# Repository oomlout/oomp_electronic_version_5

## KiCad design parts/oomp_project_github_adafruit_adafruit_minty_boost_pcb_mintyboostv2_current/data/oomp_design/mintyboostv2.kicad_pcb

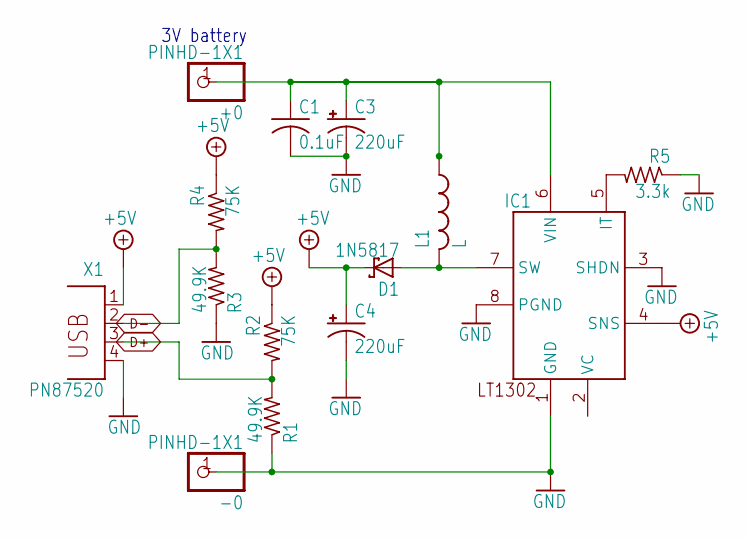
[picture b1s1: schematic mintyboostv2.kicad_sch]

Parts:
+0: PINHD-1X1; 1X01
-0: PINHD-1X1; 1X01
C1: 0.1uF; C025-025X050
C3, C4: 220uF; E2,5-5
D1: 1N5817; DO41-7
IC1: LT1302; DIL08
L1: L; 6000
R1, R3: 49.9K; 0204_5
R2, R4: 75K; 0204_5
R5: 3.3k; 0204_5
X1: PN87520

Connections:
+5V: C4.+, D1.C, IC1.4 (SNS), R2.1, R4.1, X1.1
BATT+: +0.1, C1.1, C3.+, IC1.6 (VIN), L1.1
D+: R1.2, R2.2, X1.3
D-: R3.2, R4.2, X1.2
GND: -0.1, C1.2, C3.-, C4.-, IC1.1 (GND), IC1.3 (SHDN), IC1.8 (PGND), R1.1, R3.1, R5.1, X1.4
unnamed: IC1.5 (IT), R5.2
unnamed: D1.A, IC1.7 (SW), L1.2

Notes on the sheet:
3V battery

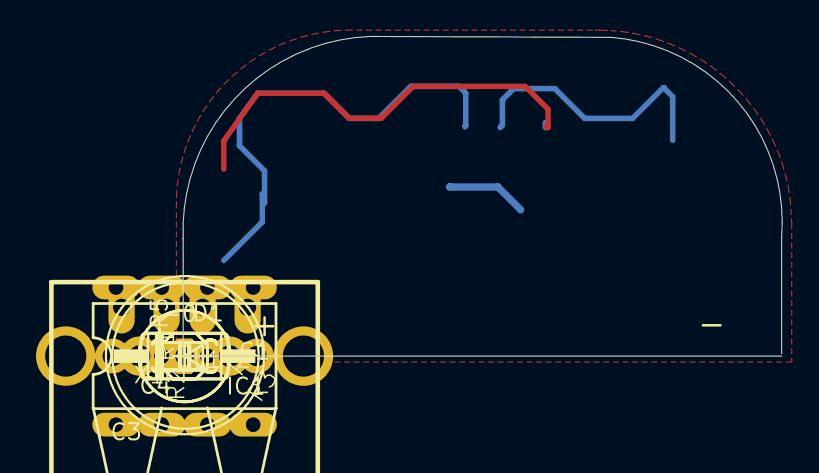
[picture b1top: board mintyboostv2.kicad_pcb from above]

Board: 16 copper layers, 33.3 x 17.8 mm, 14 parts (0 on the bottom side), 7 nets.

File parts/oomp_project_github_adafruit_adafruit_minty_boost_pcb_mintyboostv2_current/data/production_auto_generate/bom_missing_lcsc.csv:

Designator,Comment,Footprint,OOMP ID,Reason
C1,0.1uF,mintyboostv2-import-fps:C025-025X050,,No verified LCSC part number
C3,220uF,"mintyboostv2-import-fps:E2,5-5",,No verified LCSC part number
C4,220uF,"mintyboostv2-import-fps:E2,5-5",,No verified LCSC part number
D1,1N5817,mintyboostv2-import-fps:DO41-7,,No verified LCSC part number
IC1,LT1302,mintyboostv2-import-fps:DIL08,,No verified LCSC part number
L1,L,mintyboostv2-import-fps:6000,,No verified LCSC part number
R1,49.9K,mintyboostv2-import-fps:0204_5,,No verified LCSC part number
R2,75K,mintyboostv2-import-fps:0204_5,,No verified LCSC part number
R3,49.9K,mintyboostv2-import-fps:0204_5,,No verified LCSC part number
R4,75K,mintyboostv2-import-fps:0204_5,,No verified LCSC part number
R5,3.3k,mintyboostv2-import-fps:0204_5,,No verified LCSC part number
X1,,mintyboostv2-import-fps:PN87520,,No verified LCSC part number

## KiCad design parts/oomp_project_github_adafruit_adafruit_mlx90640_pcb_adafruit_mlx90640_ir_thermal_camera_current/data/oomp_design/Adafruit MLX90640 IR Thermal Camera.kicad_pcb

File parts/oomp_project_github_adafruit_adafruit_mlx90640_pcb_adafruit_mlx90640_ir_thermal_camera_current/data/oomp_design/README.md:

# OOMP KiCad design copy

Open `Adafruit MLX90640 IR Thermal Camera.kicad_pro` (or the `.kicad_pcb` / `.kicad_sch`) in KiCad. Local OOMP libraries are under `libraries/`. Original inputs are preserved in [../original/](../original/).

Only verified unchanged installed KiCad defaults were renamed. Modified, custom, unmatched and unavailable items remain unchanged. Soldering variants are never swapped during conversion. Existing pad coordinates, nets and UUIDs are preserved.

See [conversion_report.yaml](conversion_report.yaml) for every conversion and skip. Copy this directory before editing; regeneration refuses to overwrite edited design files.

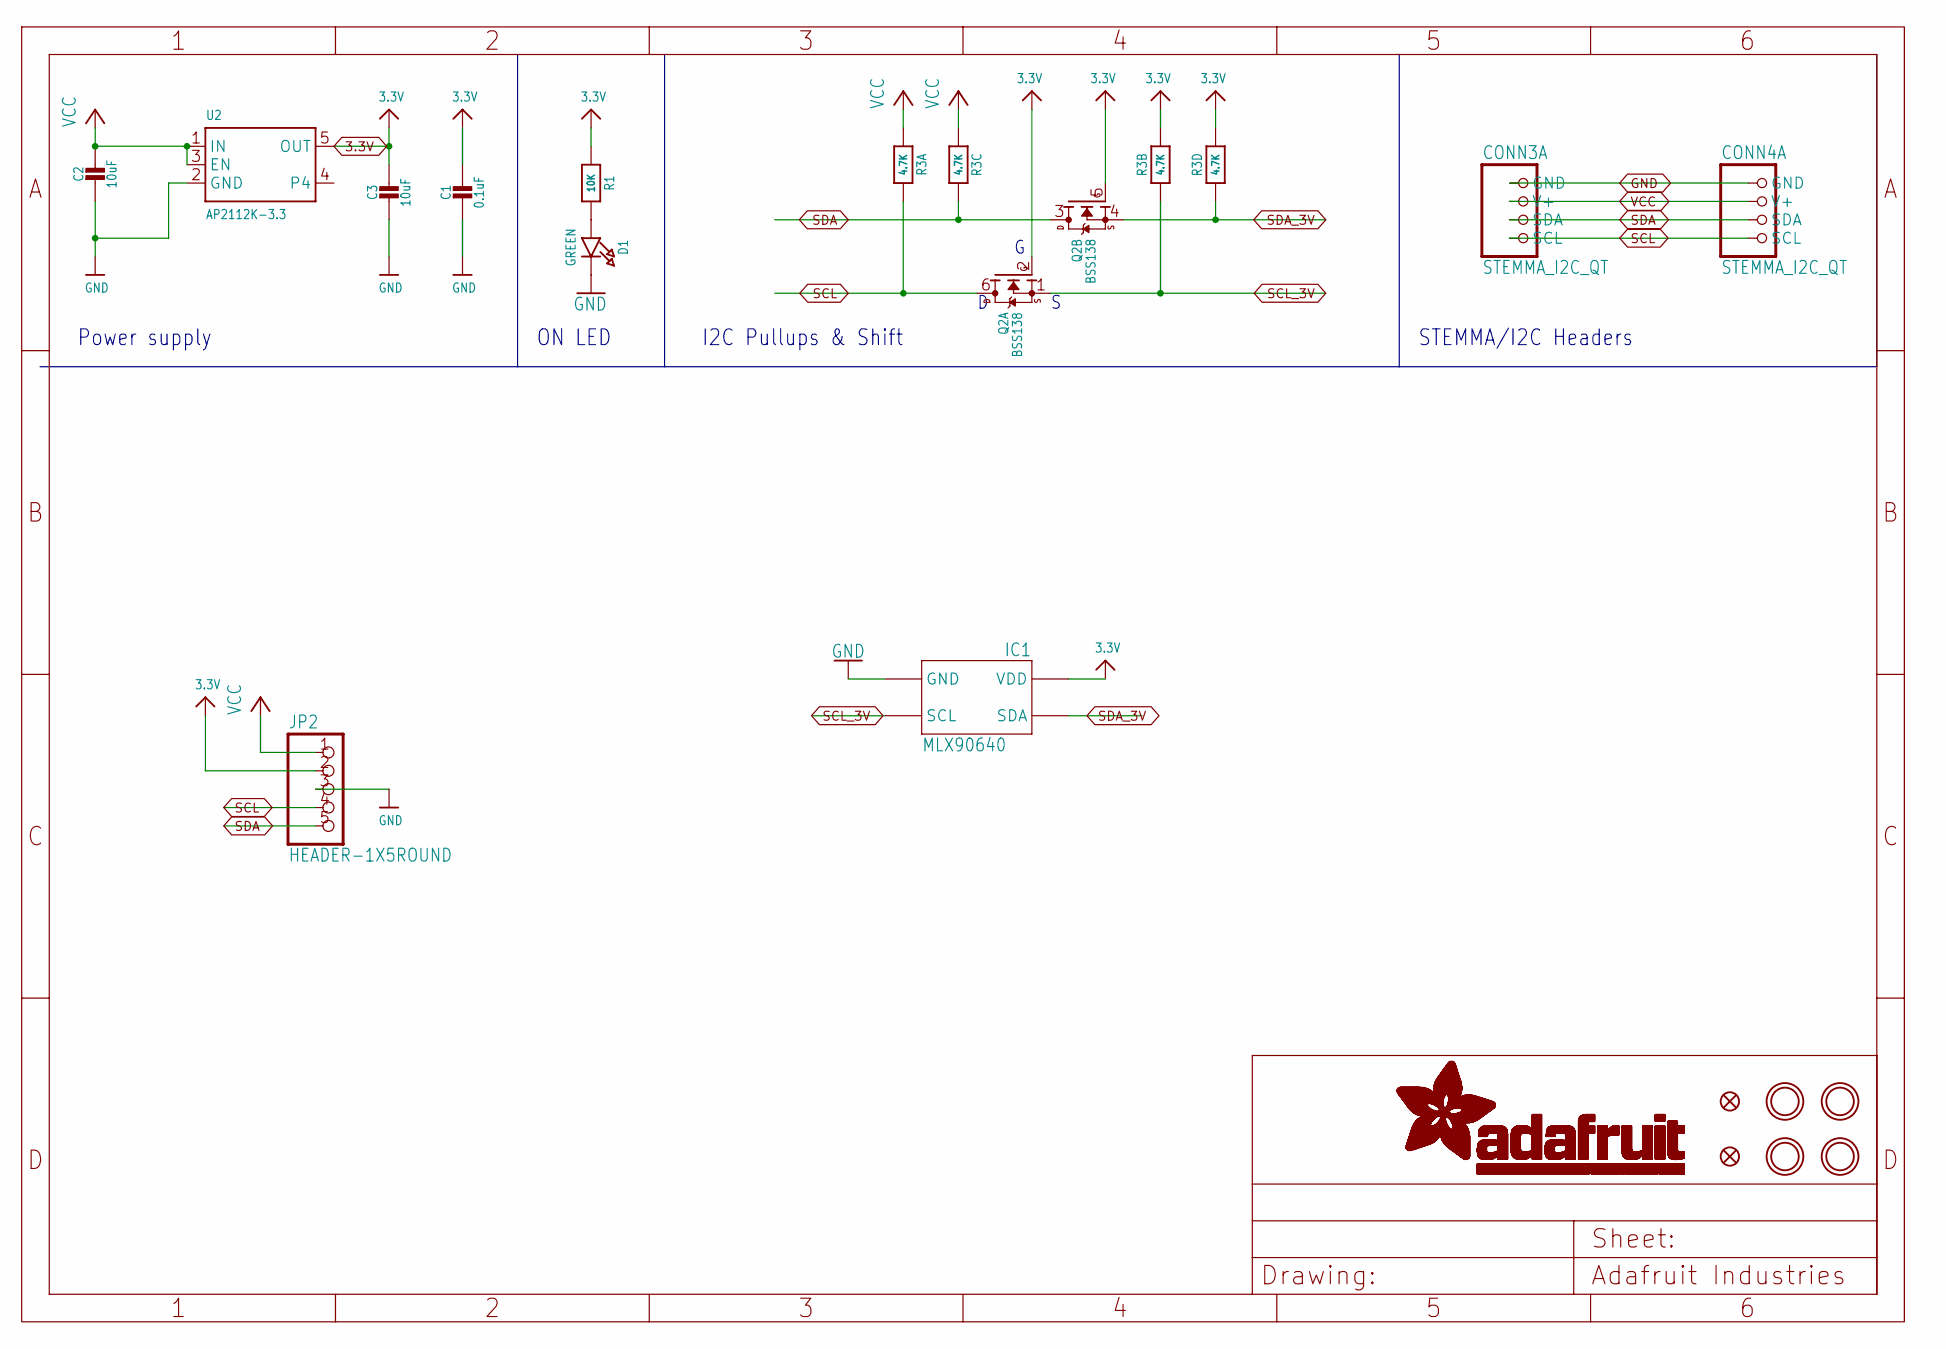
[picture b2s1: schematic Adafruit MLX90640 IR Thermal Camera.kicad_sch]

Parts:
C1: 0.1uF; 0603-NO
C2, C3: 10uF; 0805-NO
CONN3, CONN4: STEMMA_I2C_QT; JST_SH4
D1: GREEN; CHIPLED_0603_NOOUTLINE
FID3, FID4: FIDUCIAL_1MM
IC1: MLX90640
JP2: HEADER-1X5ROUND; 1X05_ROUND
Q2: BSS138; SOT363
R1: 10K; 0603-NO
R3: 4.7K; RESPACK_4X0603
U2: AP2112K-3.3; SOT23-5
U$1, U$17, U$19, U$21: MOUNTINGHOLE2.5; MOUNTINGHOLE_2.5_PLATED

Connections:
3.3V: C1.1, C3.1, IC1.VDD, JP2.2, Q2.2 (G), Q2.5 (G), R1.1, R3.2 (1), R3.4 (1), U2.5 (OUT)
GND: C1.2, C2.2, C3.2, CONN3.1 (GND), CONN4.1 (GND), D1.C, IC1.GND, JP2.3, U2.2 (GND)
unnamed: D1.A, R1.2
SCL: CONN3.4 (SCL), CONN4.4 (SCL), JP2.4, Q2.6 (D), R3.8 (2)
SCL_3V: IC1.SCL, Q2.1 (S), R3.7 (2)
SDA: CONN3.3 (SDA), CONN4.3 (SDA), JP2.5, Q2.3 (D), R3.6 (2)
SDA_3V: IC1.SDA, Q2.4 (S), R3.5 (2)
VCC: C2.1, CONN3.2 (V+), CONN4.2 (V+), JP2.1, R3.1, R3.3 (1), U2.1 (IN), U2.3 (EN)

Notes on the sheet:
I2C Pullups & Shift
STEMMA/I2C Headers
ON LED
Power supply

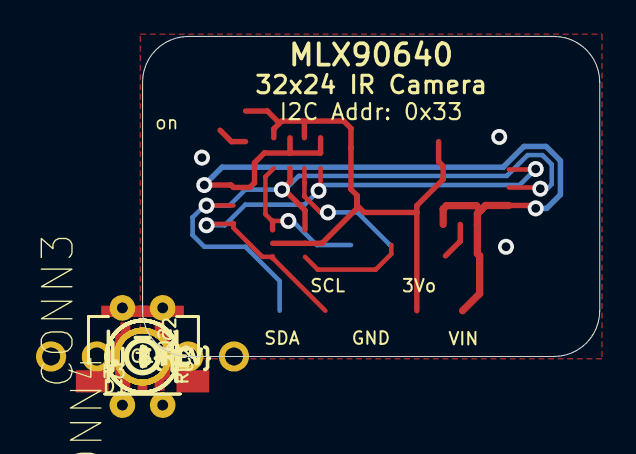
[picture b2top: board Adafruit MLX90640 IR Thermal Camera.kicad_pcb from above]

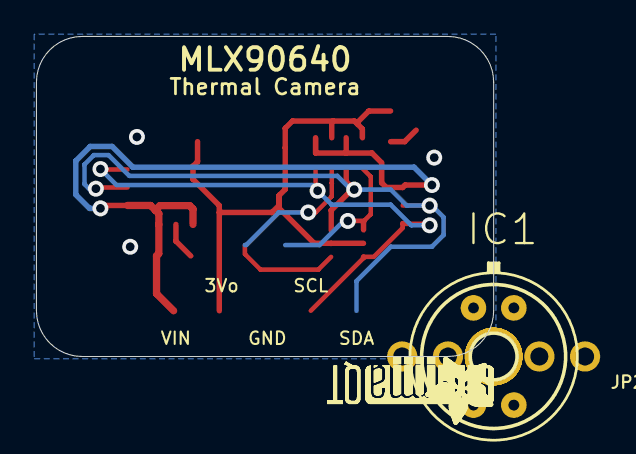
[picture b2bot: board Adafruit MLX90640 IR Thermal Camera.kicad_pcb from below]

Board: 2 copper layers, 25.4 x 17.8 mm, 23 parts (6 on the bottom side), 8 nets.

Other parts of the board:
U$4, U$22: ADAFRUIT_3.5MM
U$25: PCBFEAT-REV-040
U$30, U$31: STEMMAQT

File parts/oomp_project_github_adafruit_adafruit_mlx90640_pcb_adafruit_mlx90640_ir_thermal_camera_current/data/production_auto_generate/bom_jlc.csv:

Comment,Designator,Footprint,LCSC Part #
,JP2,Adafruit MLX90640 IR Thermal Camera-import-fps:1X05_ROUND,C42431835
,"U$4,U$22",Adafruit MLX90640 IR Thermal Camera-import-fps:ADAFRUIT_3.5MM,
,U$25,Adafruit MLX90640 IR Thermal Camera-import-fps:PCBFEAT-REV-040,
,"U$30,U$31",Adafruit MLX90640 IR Thermal Camera-import-fps:STEMMAQT,
0.1uF,C1,Adafruit MLX90640 IR Thermal Camera-import-fps:0603-NO,C14663
10K,R1,Adafruit MLX90640 IR Thermal Camera-import-fps:0603-NO,C98220
10uF,"C2,C3",Adafruit MLX90640 IR Thermal Camera-import-fps:0805-NO,
4.7K,R3,Adafruit MLX90640 IR Thermal Camera-import-fps:RESPACK_4X0603,C23162
AP2112K-3.3,U2,Adafruit MLX90640 IR Thermal Camera-import-fps:SOT23-5,
BSS138,Q2,Adafruit MLX90640 IR Thermal Camera-import-fps:SOT363,
GREEN,D1,Adafruit MLX90640 IR Thermal Camera-import-fps:CHIPLED_0603_NOOUTLINE,
MLX90640,IC1,Adafruit MLX90640 IR Thermal Camera-import-fps:MLX90640,
STEMMA_I2C_QT,"CONN3,CONN4",Adafruit MLX90640 IR Thermal Camera-import-fps:JST_SH4,C160404

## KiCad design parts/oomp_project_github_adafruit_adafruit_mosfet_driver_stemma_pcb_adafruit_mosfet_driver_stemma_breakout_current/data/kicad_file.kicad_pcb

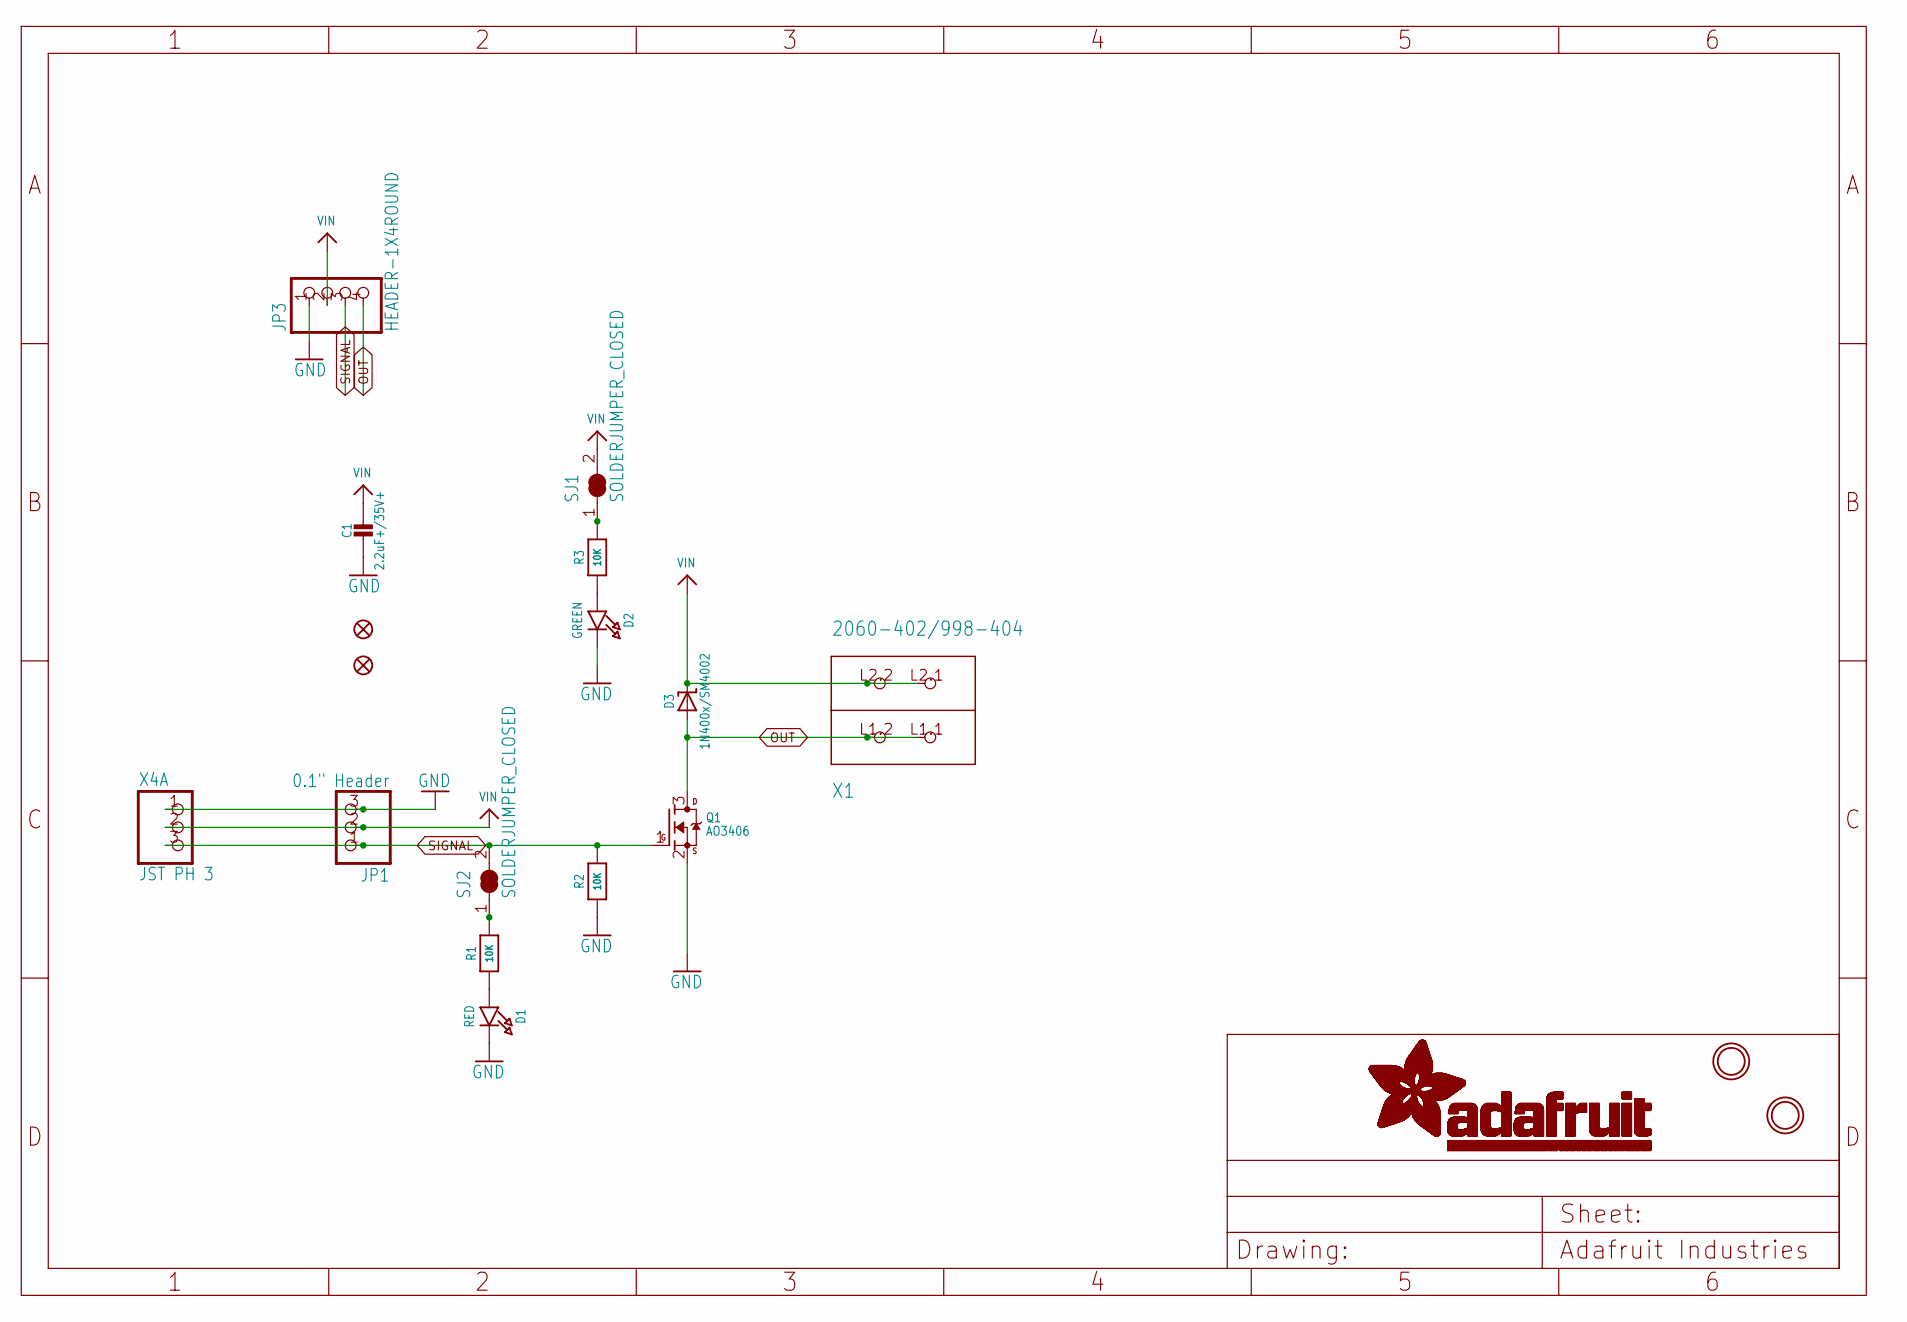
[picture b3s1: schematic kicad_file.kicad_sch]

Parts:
C1: 2.2uF+/35V+; 0805-NO
D1: RED; CHIPLED_0603_NOOUTLINE
D2: GREEN; CHIPLED_0603_NOOUTLINE
D3: 1N400x/SM4002; SOD-123
FID2, FID3: FIDUCIAL_1MM
JP1: 0.1" Header; 1X03_OVAL
JP3: HEADER-1X4ROUND; 1X04_ROUND
Q1: AO3406; SOT23-WIDE
R1, R2, R3: 10K; 0603-NO
SJ1, SJ2: SOLDERJUMPER_CLOSED; SOLDERJUMPER_CLOSEDWIRE
U$1, U$8: MOUNTINGHOLE2.5; MOUNTINGHOLE_2.5_PLATED
X1: 2060-402/998-404; P-2060-402_998-404
X4: JST PH 3; JSTPH3

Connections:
GND: C1.2, D1.C, D2.C, JP1.3, JP3.1, Q1.2 (S), R2.1, X4.1
unnamed: R3.2, SJ1.1
unnamed: D1.A, R1.1
unnamed: R1.2, SJ2.1
unnamed: D2.A, R3.1
OUT: D3.A, JP3.4, Q1.3 (D), X1.L1.1 (P1.1), X1.L1.2 (P1.2)
SIGNAL: JP1.1, JP3.3, Q1.1 (G), R2.2, SJ2.2, X4.3
VIN: C1.1, D3.C, JP1.2, JP3.2, SJ1.2, X1.L2.1 (P2.1), X1.L2.2 (P2.2), X4.2

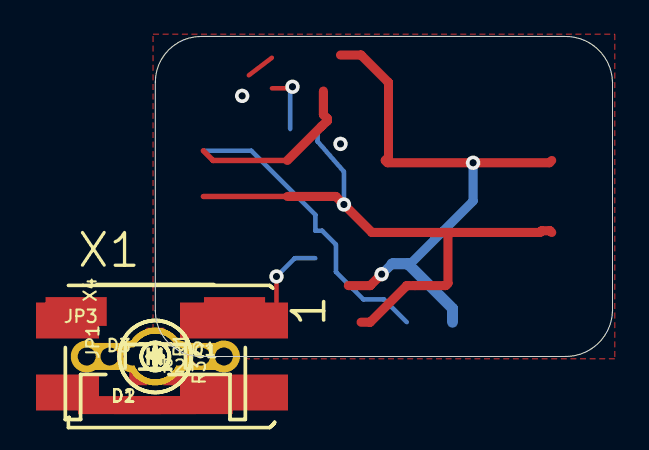
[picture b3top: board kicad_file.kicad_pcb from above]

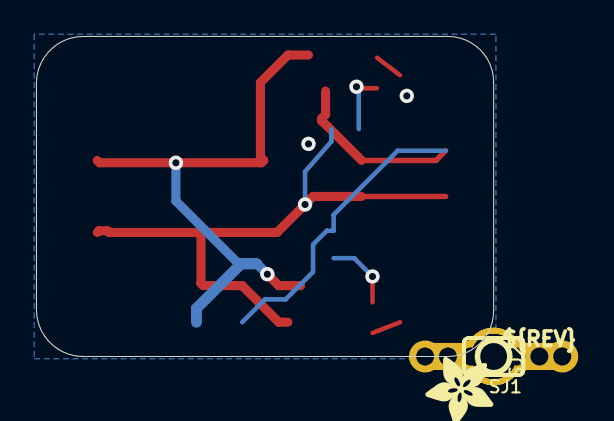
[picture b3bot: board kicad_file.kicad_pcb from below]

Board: 16 copper layers, 25.4 x 17.8 mm, 36 parts (15 on the bottom side), 8 nets.

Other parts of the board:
PLABEL0: PLABEL0
PLABEL1: PLABEL1
PLABEL2: PLABEL2
PLABEL3: PLABEL3
PLABEL4: PLABEL4
PLABEL5: PLABEL5
PLABEL6: PLABEL6
PLABEL7: PLABEL7
PLABEL8: PLABEL8
PLABEL9: PLABEL9
PLABEL10: PLABEL10
PLABEL11: PLABEL11
PLABEL12: PLABEL12
PLABEL13: PLABEL13
U$3: SYMBOL_PLUS
U$5: PCBFEAT-REV-040
U$9: SYMBOL_MINUS
U$12: ADAFRUIT_3.5MM

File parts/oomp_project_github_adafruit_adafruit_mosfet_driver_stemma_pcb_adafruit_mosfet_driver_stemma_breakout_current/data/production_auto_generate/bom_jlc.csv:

Comment,Designator,Footprint,LCSC Part #
,JP3,Adafruit MOSFET Driver STEMMA Breakout-import-fps:1X04_ROUND,C42431795
,U$12,Adafruit MOSFET Driver STEMMA Breakout-import-fps:ADAFRUIT_3.5MM,
,U$5,Adafruit MOSFET Driver STEMMA Breakout-import-fps:PCBFEAT-REV-040,
,PLABEL0,Adafruit MOSFET Driver STEMMA Breakout-import-fps:PLABEL0,
,PLABEL1,Adafruit MOSFET Driver STEMMA Breakout-import-fps:PLABEL1,
,PLABEL10,Adafruit MOSFET Driver STEMMA Breakout-import-fps:PLABEL10,
,PLABEL11,Adafruit MOSFET Driver STEMMA Breakout-import-fps:PLABEL11,
,PLABEL12,Adafruit MOSFET Driver STEMMA Breakout-import-fps:PLABEL12,
,PLABEL13,Adafruit MOSFET Driver STEMMA Breakout-import-fps:PLABEL13,
,PLABEL2,Adafruit MOSFET Driver STEMMA Breakout-import-fps:PLABEL2,
,PLABEL3,Adafruit MOSFET Driver STEMMA Breakout-import-fps:PLABEL3,
,PLABEL4,Adafruit MOSFET Driver STEMMA Breakout-import-fps:PLABEL4,
,PLABEL5,Adafruit MOSFET Driver STEMMA Breakout-import-fps:PLABEL5,
,PLABEL6,Adafruit MOSFET Driver STEMMA Breakout-import-fps:PLABEL6,
,PLABEL7,Adafruit MOSFET Driver STEMMA Breakout-import-fps:PLABEL7,
,PLABEL8,Adafruit MOSFET Driver STEMMA Breakout-import-fps:PLABEL8,
,PLABEL9,Adafruit MOSFET Driver STEMMA Breakout-import-fps:PLABEL9,
,U$9,Adafruit MOSFET Driver STEMMA Breakout-import-fps:SYMBOL_MINUS,
,U$3,Adafruit MOSFET Driver STEMMA Breakout-import-fps:SYMBOL_PLUS,
"0.1"" Header",JP1,Adafruit MOSFET Driver STEMMA Breakout-import-fps:1X03_OVAL,C49257
10K,"R1,R2,R3",Adafruit MOSFET Driver STEMMA Breakout-import-fps:0603-NO,C98220
1N400x/SM4002,D3,Adafruit MOSFET Driver STEMMA Breakout-import-fps:SOD-123,
2.2uF+/35V+,C1,Adafruit MOSFET Driver STEMMA Breakout-import-fps:0805-NO,
2060-402/998-404,X1,Adafruit MOSFET Driver STEMMA Breakout-import-fps:P-2060-402_998-404,
AO3406,Q1,Adafruit MOSFET Driver STEMMA Breakout-import-fps:SOT23-WIDE,
GREEN,D2,Adafruit MOSFET Driver STEMMA Breakout-import-fps:CHIPLED_0603_NOOUTLINE,
JST PH 3,X4,Adafruit MOSFET Driver STEMMA Breakout-import-fps:JSTPH3,
RED,D1,Adafruit MOSFET Driver STEMMA Breakout-import-fps:CHIPLED_0603_NOOUTLINE,

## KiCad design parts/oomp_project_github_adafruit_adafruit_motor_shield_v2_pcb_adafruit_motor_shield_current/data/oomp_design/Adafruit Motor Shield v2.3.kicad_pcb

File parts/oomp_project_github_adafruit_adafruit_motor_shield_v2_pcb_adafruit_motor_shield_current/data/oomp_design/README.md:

# OOMP KiCad design copy

Open `Adafruit Motor Shield v2.3.kicad_pro` (or the `.kicad_pcb` / `.kicad_sch`) in KiCad. Local OOMP libraries are under `libraries/`. Original inputs are preserved in [../original/](../original/).

Only verified unchanged installed KiCad defaults were renamed. Modified, custom, unmatched and unavailable items remain unchanged. Soldering variants are never swapped during conversion. Existing pad coordinates, nets and UUIDs are preserved.

See [conversion_report.yaml](conversion_report.yaml) for every conversion and skip. Copy this directory before editing; regeneration refuses to overwrite edited design files.

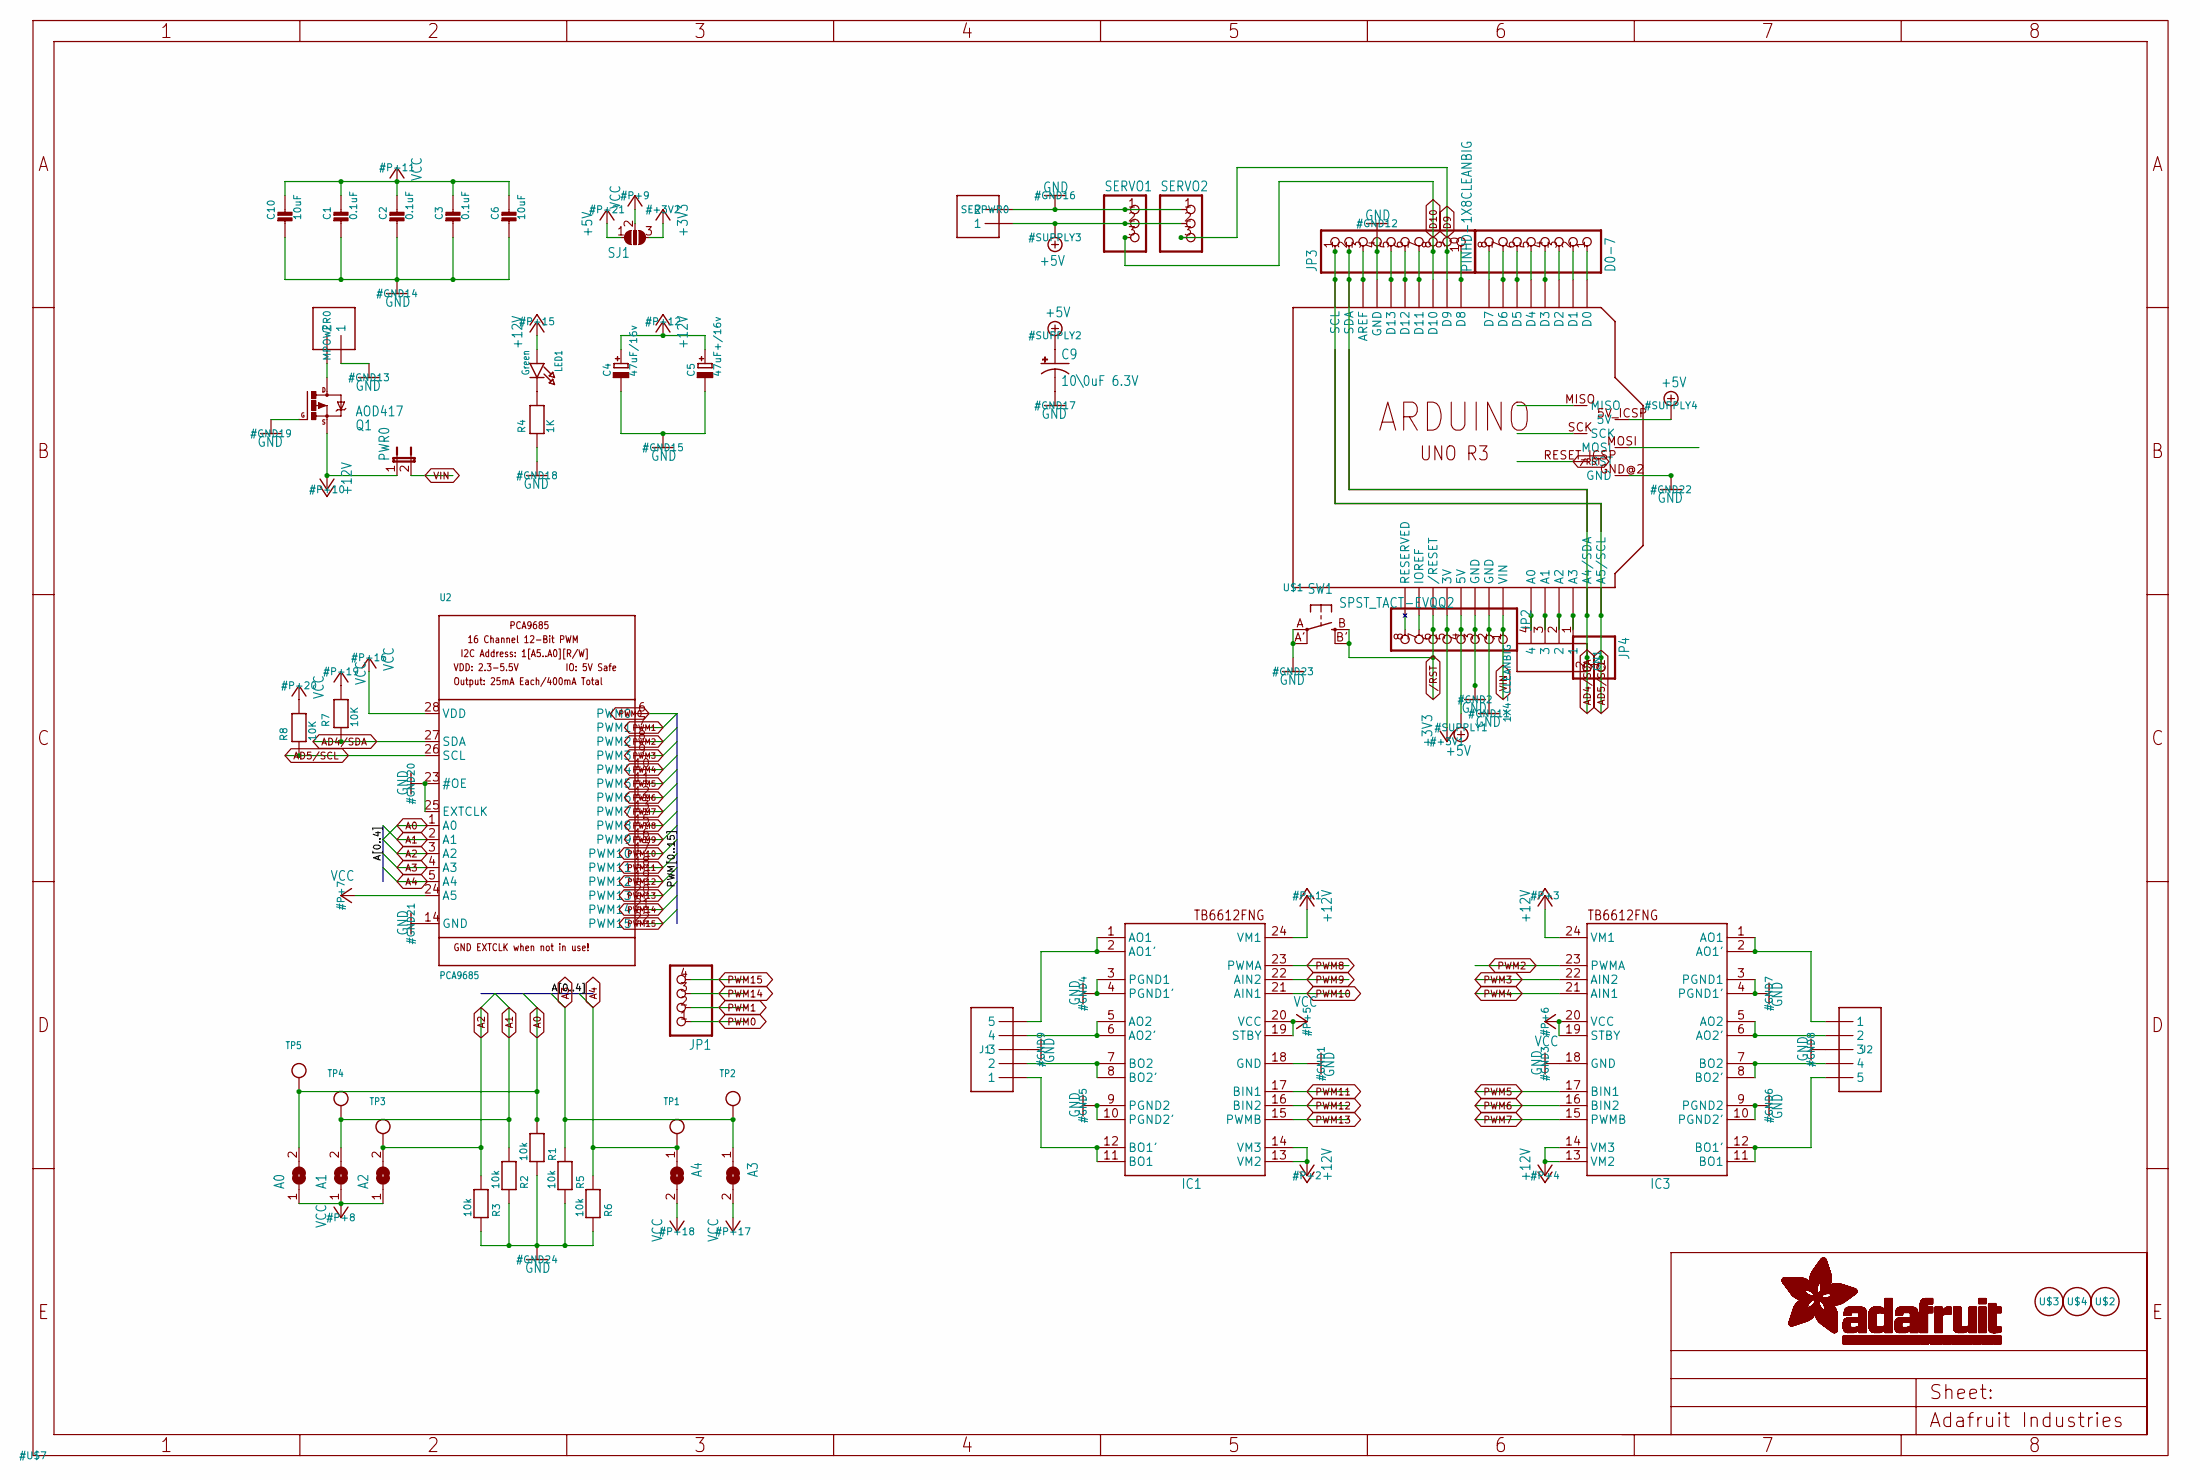
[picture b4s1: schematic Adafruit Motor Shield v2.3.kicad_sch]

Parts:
A0, A1, A2, A3, A4: SOLDERJUMPERREFLOW_NOPASTE; SOLDERJUMPER_REFLOW_NOPASTE
C1, C2, C3: 0.1uF; 0805-NO
C4: 47uF/16v; PANASONIC_C
C5: 47uF+/16v; PANASONIC_C
C6, C10: 10uF; 0805-NO
C9: 10\0uF 6.3V; PANASONIC_C
CN1: 1X4-CLEANBIG; 1X04-CLEANBIG
D0-7: PINHD-1X8CLEANBIG; 1X08-CLEANBIG
IC1, IC3: TB6612FNG; SSOP24
J1, J2: 1X5; 1X05-3.5MM
JP1: HEADER-1X476MIL; 1X04_ROUND_76
JP2: PINHD-1X8CLEANBIG; 1X08-CLEANBIG
JP3: HEADER-1X1070MIL; 1X10_ROUND70
JP4: HEADER-1X2ROUND; 1X02_ROUND
LED1: Green; CHIPLED_0805_NOOUTLINE
MPOWER0: 1X2-3.5MM
PWR0: JP1E; JP1
Q1: AOD417; D-PAK_TO252AA
R1, R2, R3, R5, R6: 10k; 0805-NO
R4: 1K; 0805-NO
R7, R8: 10K; 0805-NO
SERPWR0: 1X2-3.5MM
SERVO1, SERVO2: PINHD-1X3; 1X03
SJ1: SOLDERJUMPER_2WAY; SOLDERJUMPER_2WAY_OPEN_NOPASTE
SW1: SPST_TACT-EVQQ2; EVQ-Q2
TP1, TP2, TP3, TP4, TP5: TESTPOINTROUND2MM; TESTPOINT_ROUND_2MM
U2: PCA9685; TSSOP28
U$1: ARDUINO_R3_ICSP; ARDUINOR3_ICSP
U$2, U$3, U$4: FIDUCIAL; FIDUCIAL_1MM

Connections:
+3V3: JP2.5, SJ1.3, U$1.3V
+5V: C9.+, JP2.4, SERPWR0.1, SERVO1.2, SERVO2.2, SJ1.1, U$1.5V, U$1.5V_ICSP (5V)
+12V: C4.+, C5.+, IC1.13 (VM2), IC1.14 (VM3), IC1.24 (VM1), IC3.13 (VM2), IC3.14 (VM3), IC3.24 (VM1), LED1.A, PWR0.1, Q1.3 (S)
/RST: JP2.6, SW1.B (S), SW1.B' (S1), U$1.RESET (/RESET), U$1.RESET_ICSP (RST)
A0: A0.2, R1.2, TP5.P$1, U2.1 (A0)
A1: A1.2, R2.2, TP4.P$1, U2.2 (A1)
A2: A2.2, R3.2, TP3.P$1, U2.3 (A2)
A3: A3.1, R5.2, TP2.P$1, U2.4 (A3)
A4: A4.1, R6.2, TP1.P$1, U2.5 (A4)
AD0: CN1.4, U$1.A0
AD1: CN1.3, U$1.A1
AD2: CN1.2, U$1.A2
AD3: CN1.1, U$1.A3
AD4/SDA: JP3.2, JP4.2, R7.1, U2.27 (SDA), U$1.A4 (A4/SDA), U$1.SDA
AD5/SCL: JP3.1, JP4.1, R8.1, U2.26 (SCL), U$1.A5 (A5/SCL), U$1.SCL
AREF: JP3.3, U$1.AREF
D0: D0-7.1, U$1.D0
D1: D0-7.2, U$1.D1
D2: D0-7.3, U$1.D2
D3: D0-7.4, U$1.D3
D4: D0-7.5, U$1.D4
D5: D0-7.6, U$1.D5
D6: D0-7.7, U$1.D6
D7: D0-7.8, U$1.D7
D8: JP3.10, U$1.D8
D9: JP3.9, SERVO2.3, U$1.D9
D10: JP3.8, SERVO1.3, U$1.D10
D11: JP3.7, U$1.D11
D12: JP3.6, U$1.D12
D13: JP3.5, U$1.D13
GND: C1.2, C2.2, C3.2, C4.-, C5.-, C6.2, C9.-, C10.2, IC1.3 (PGND1), IC1.4 (PGND1'), IC1.9 (PGND2), IC1.10 (PGND2'), IC1.18 (GND), IC3.3 (PGND1), IC3.4 (PGND1'), IC3.9 (PGND2), IC3.10 (PGND2'), IC3.18 (GND), J1.3, J2.3, JP2.2, JP2.3, JP3.4, MPOWER0.1, Q1.1 (G), R1.1, R2.1, R3.1, R4.1, R5.1, R6.1, SERPWR0.2, SERVO1.1, SERVO2.1, SW1.A, SW1.A' (P1), U2.14 (GND), U2.23 (#OE), U2.25 (EXTCLK), U$1.GND, U$1.GND@1 (GND), U$1.GND@2 (GND), U$1.GND@3 (GND)
IOREF: JP2.7, U$1.IOREF
M1A: IC1.1 (AO1), IC1.2 (AO1'), J1.5
M1B: IC1.5 (AO2), IC1.6 (AO2'), J1.4
M2A: IC1.11 (BO1), IC1.12 (BO1'), J1.1
M2B: IC1.7 (BO2), IC1.8 (BO2'), J1.2
M3A: IC3.1 (AO1), IC3.2 (AO1'), J2.1
M3B: IC3.5 (AO2), IC3.6 (AO2'), J2.2
M4A: IC3.11 (BO1), IC3.12 (BO1'), J2.5
M4B: IC3.7 (BO2), IC3.8 (BO2'), J2.4
MISO: U$1.MISO
MOSI: U$1.MOSI
unnamed: JP2.8, U$1.RESERVED
unnamed: LED1.C, R4.2
PWM0: JP1.1, U2.6 (PWM0)
PWM1: JP1.2, U2.7 (PWM1)
PWM2: IC3.23 (PWMA), U2.8 (PWM2)
PWM3: IC3.22 (AIN2), U2.9 (PWM3)
PWM4: IC3.21 (AIN1), U2.10 (PWM4)
PWM5: IC3.17 (BIN1), U2.11 (PWM5)
PWM6: IC3.16 (BIN2), U2.12 (PWM6)
PWM7: IC3.15 (PWMB), U2.13 (PWM7)
PWM8: IC1.23 (PWMA), U2.15 (PWM8)
PWM9: IC1.22 (AIN2), U2.16 (PWM9)
PWM10: IC1.21 (AIN1), U2.17 (PWM10)
PWM11: IC1.17 (BIN1), U2.18 (PWM11)
PWM12: IC1.16 (BIN2), U2.19 (PWM12)
PWM13: IC1.15 (PWMB), U2.20 (PWM13)
PWM14: JP1.3, U2.21 (PWM14)
PWM15: JP1.4, U2.22 (PWM15)
SCK: U$1.SCK
VCC: A0.1, A1.1, A2.1, A3.2, A4.2, C1.1, C2.1, C3.1, C6.1, C10.1, IC1.19 (STBY), IC1.20 (VCC), IC3.19 (STBY), IC3.20 (VCC), R7.2, R8.2, SJ1.2, U2.24 (A5), U2.28 (VDD)
VIN: JP2.1, PWR0.2, U$1.VIN
VMOTOR: MPOWER0.2, Q1.4 (D)

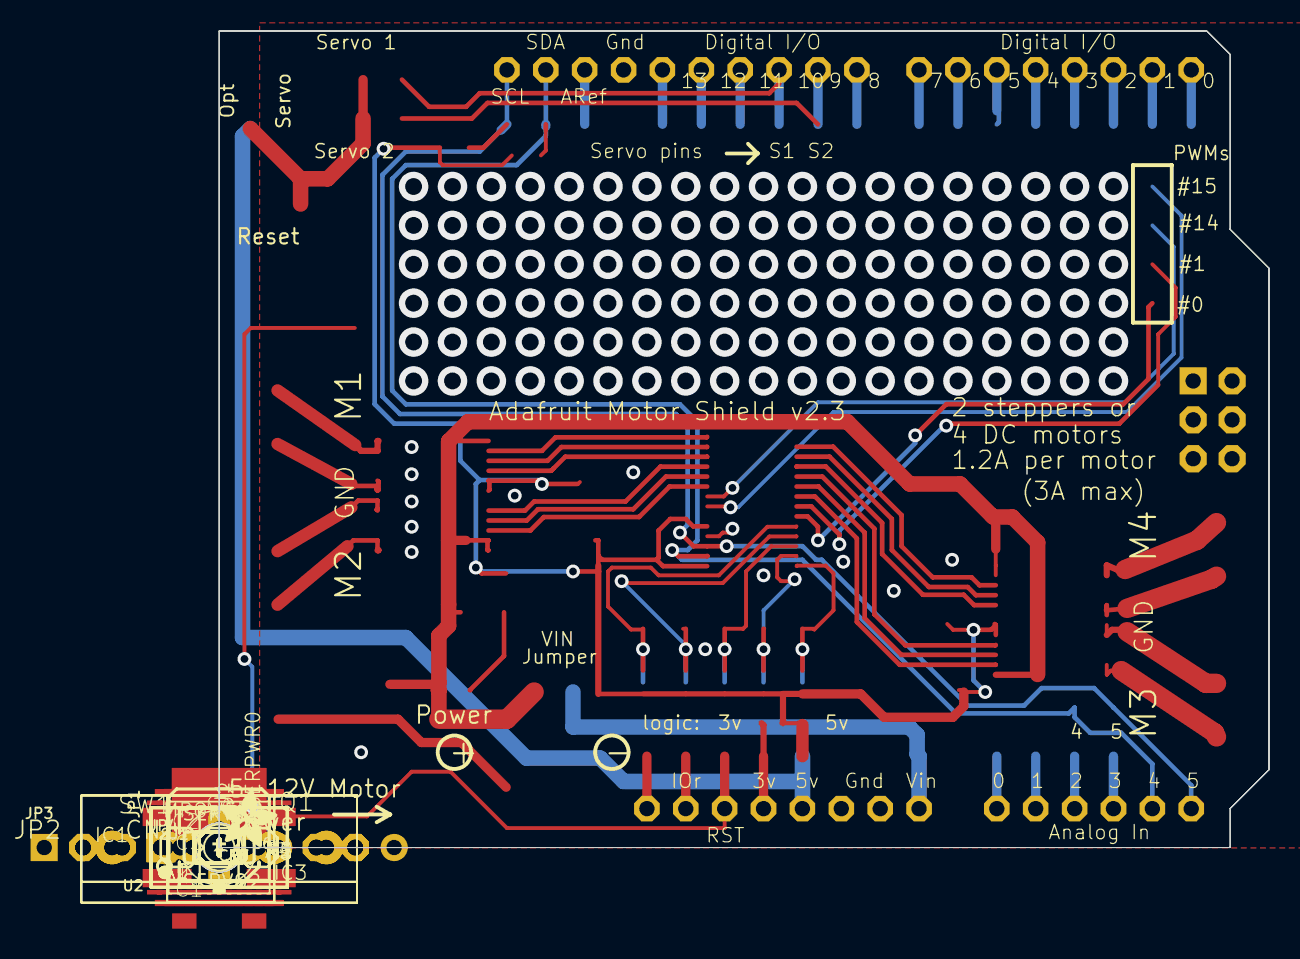
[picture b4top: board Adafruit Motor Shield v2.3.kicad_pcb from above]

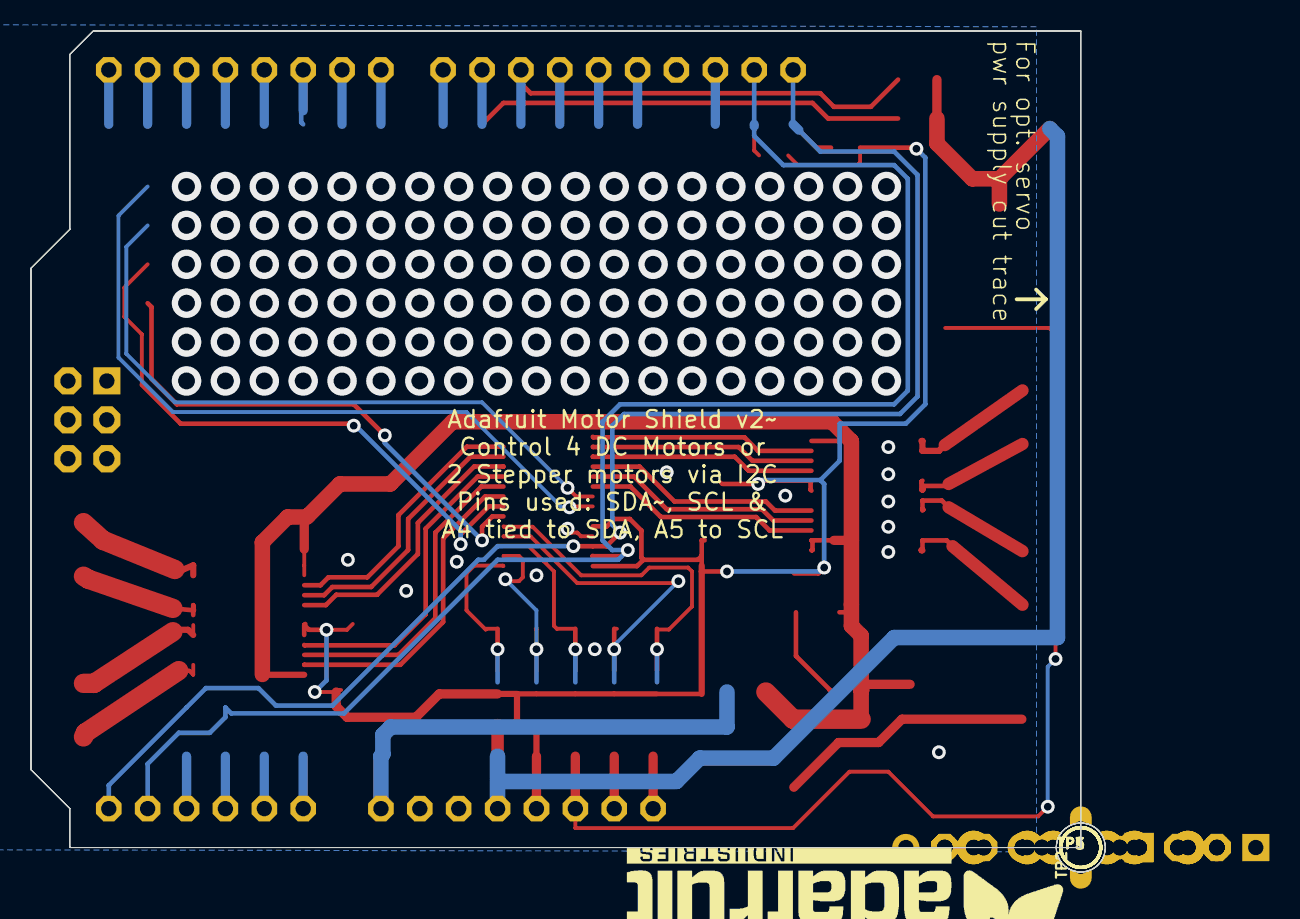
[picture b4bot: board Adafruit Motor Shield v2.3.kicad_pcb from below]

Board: 16 copper layers, 68.6 x 53.3 mm, 55 parts (6 on the bottom side), 61 nets.

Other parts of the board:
U$5: ADAFRUIT_TEXT_30MM
U$6: ADAFRUIT_3.5MM
UNK_HOLE_0: dummyfp0
UNK_HOLE_1: dummyfp1
UNK_HOLE_2: dummyfp2

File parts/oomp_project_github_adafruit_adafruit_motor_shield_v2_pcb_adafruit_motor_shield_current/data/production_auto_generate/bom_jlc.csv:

Comment,Designator,Footprint,LCSC Part #
,JP4,Adafruit Motor Shield v2.3-import-fps:1X02_ROUND,C492401
,"SERVO1,SERVO2",Adafruit Motor Shield v2.3-import-fps:1X03,C49257
,JP1,Adafruit Motor Shield v2.3-import-fps:1X04_ROUND_76,C42431795
,D0-7,Adafruit Motor Shield v2.3-import-fps:1X08-CLEANBIG,
,JP2,Adafruit Motor Shield v2.3-import-fps:1X08-CLEANBIG,C492421
,JP3,Adafruit Motor Shield v2.3-import-fps:1X10_ROUND70,C57369
,U$6,Adafruit Motor Shield v2.3-import-fps:ADAFRUIT_3.5MM,
,U$5,Adafruit Motor Shield v2.3-import-fps:ADAFRUIT_TEXT_30MM,
,PWR0,Adafruit Motor Shield v2.3-import-fps:JP1,
,"A0,A1,A2,A3,A4",Adafruit Motor Shield v2.3-import-fps:SOLDERJUMPER_REFLOW_NOPASTE,
,"TP1,TP2,TP3,TP4,TP5",Adafruit Motor Shield v2.3-import-fps:TESTPOINT_ROUND_2MM,
0.1uF,"C1,C2,C3",Adafruit Motor Shield v2.3-import-fps:0805-NO,
10\0uF 6.3V,C9,Adafruit Motor Shield v2.3-import-fps:PANASONIC_C,
10k,"R1,R2,R3,R5,R6",Adafruit Motor Shield v2.3-import-fps:0805-NO,C17414
10K,"R7,R8",Adafruit Motor Shield v2.3-import-fps:0805-NO,C17414
10uF,"C6,C10",Adafruit Motor Shield v2.3-import-fps:0805-NO,
1K,R4,Adafruit Motor Shield v2.3-import-fps:0805-NO,C17513
1X2-3.5MM,"MPOWER0,SERPWR0",Adafruit Motor Shield v2.3-import-fps:1X2-3.5MM,C492401
1X4-CLEANBIG,CN1,Adafruit Motor Shield v2.3-import-fps:1X04-CLEANBIG,
1X5,"J1,J2",Adafruit Motor Shield v2.3-import-fps:1X05-3.5MM,C42431835
47uF+/16v,C5,Adafruit Motor Shield v2.3-import-fps:PANASONIC_C,
47uF/16v,C4,Adafruit Motor Shield v2.3-import-fps:PANASONIC_C,
AOD417,Q1,Adafruit Motor Shield v2.3-import-fps:D-PAK_TO252AA,
ARDUINO_R3_ICSP,U$1,Adafruit Motor Shield v2.3-import-fps:ARDUINOR3_ICSP,
FIDUCIAL,"U$2,U$3,U$4",Adafruit Motor Shield v2.3-import-fps:FIDUCIAL_1MM,
Green,LED1,Adafruit Motor Shield v2.3-import-fps:CHIPLED_0805_NOOUTLINE,
PCA9685,U2,Adafruit Motor Shield v2.3-import-fps:TSSOP28,
SPST_TACT-EVQQ2,SW1,Adafruit Motor Shield v2.3-import-fps:EVQ-Q2,
TB6612FNG,"IC1,IC3",Adafruit Motor Shield v2.3-import-fps:SSOP24,
